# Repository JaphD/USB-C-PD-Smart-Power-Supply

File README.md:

# PD Smart Supply

A USB-C Power Delivery supply designed by Yafet Daniel. Rev A uses an STM32 controller to select a PD voltage, control a protected output, and measure output voltage and current. An OLED and three pushbuttons provide the user interface.

## Specifications

| Parameter | Design specification |
|---|---|
| Input | USB-C Power Delivery through a CH224A controller |
| Output voltage selections | 5 V, 9 V, 12 V, and 20 V |
| Rated output | Up to 3 A total, 60 W at 20 V |
| Output connectors | Two parallel screw terminals sharing one protected output |
| Controller | STM32G071CBT6 |
| Output protection | TPS259470L eFuse with MCU shutdown and fault monitoring |
| Hardware current limit | Approximately 3.76 A nominal; rated output remains 3 A |
| Monitoring | Output voltage and current sensing through the MCU ADC |
| User interface | I²C OLED, Up/Down/Select buttons, and PD status LED |
| Internal power rail | 3.3 V from a TPS560430 buck converter |
| Debug interface | SWD |
| PCB | 70 × 50 mm, four layers, nominal 1.6 mm thickness |

Available output voltages and power depend on the connected PD source and cable. Voltage selection uses discrete PD requests; the design does not provide continuously variable voltage or programmable constant-current regulation. The two outputs share the 3 A rating. The design excludes 15 V and 28 V operation.

## Hardware

The USB-C input feeds the protected output through the eFuse. A separate buck converter powers the controller and interface from the negotiated input voltage. The hardware includes VBUS transient protection, output overvoltage cutoff, controlled startup, and voltage/current test points.

## Project status

The Rev A schematic and four-layer PCB layout are complete and prepared for manufacturing. The repository includes a generated STM32CubeIDE project configured for a 64 MHz system clock, ADC voltage and current sensing, I²C, control and status GPIO, and SWD debugging. PD selection logic, display operation, button handling, and application fault handling remain to be implemented. The ratings above are design targets, not measured performance results.

## Repository contents

- `PD Smart Supply.kicad_pro`, `.kicad_sch`, and `.kicad_pcb`: KiCad project, schematic, and board layout.
- `PD Smart Supply.kicad_dru`: project-specific PCB design rules.
- `Firmware/`: STM32CubeMX configuration, STM32CubeIDE project files, generated firmware sources, and device libraries.
- `Docs/PD_Smart_Supply_Rev_A_Design_Record.pdf`: design record.
- `Docs/Sim/`: LTspice eFuse enable/shutdown simulation.
- `Docs/images/`: PCB layout and 3D render images.

Open `PD Smart Supply.kicad_pro` in KiCad 9 to inspect the hardware. Custom libraries and manufacturer references under `Lib/` and `Docs/Ref/` are excluded from Git, so library paths may need to be restored for editing. Open `Firmware/Firmware.ioc` in STM32CubeMX or import `Firmware/` into STM32CubeIDE to inspect or regenerate the firmware project.

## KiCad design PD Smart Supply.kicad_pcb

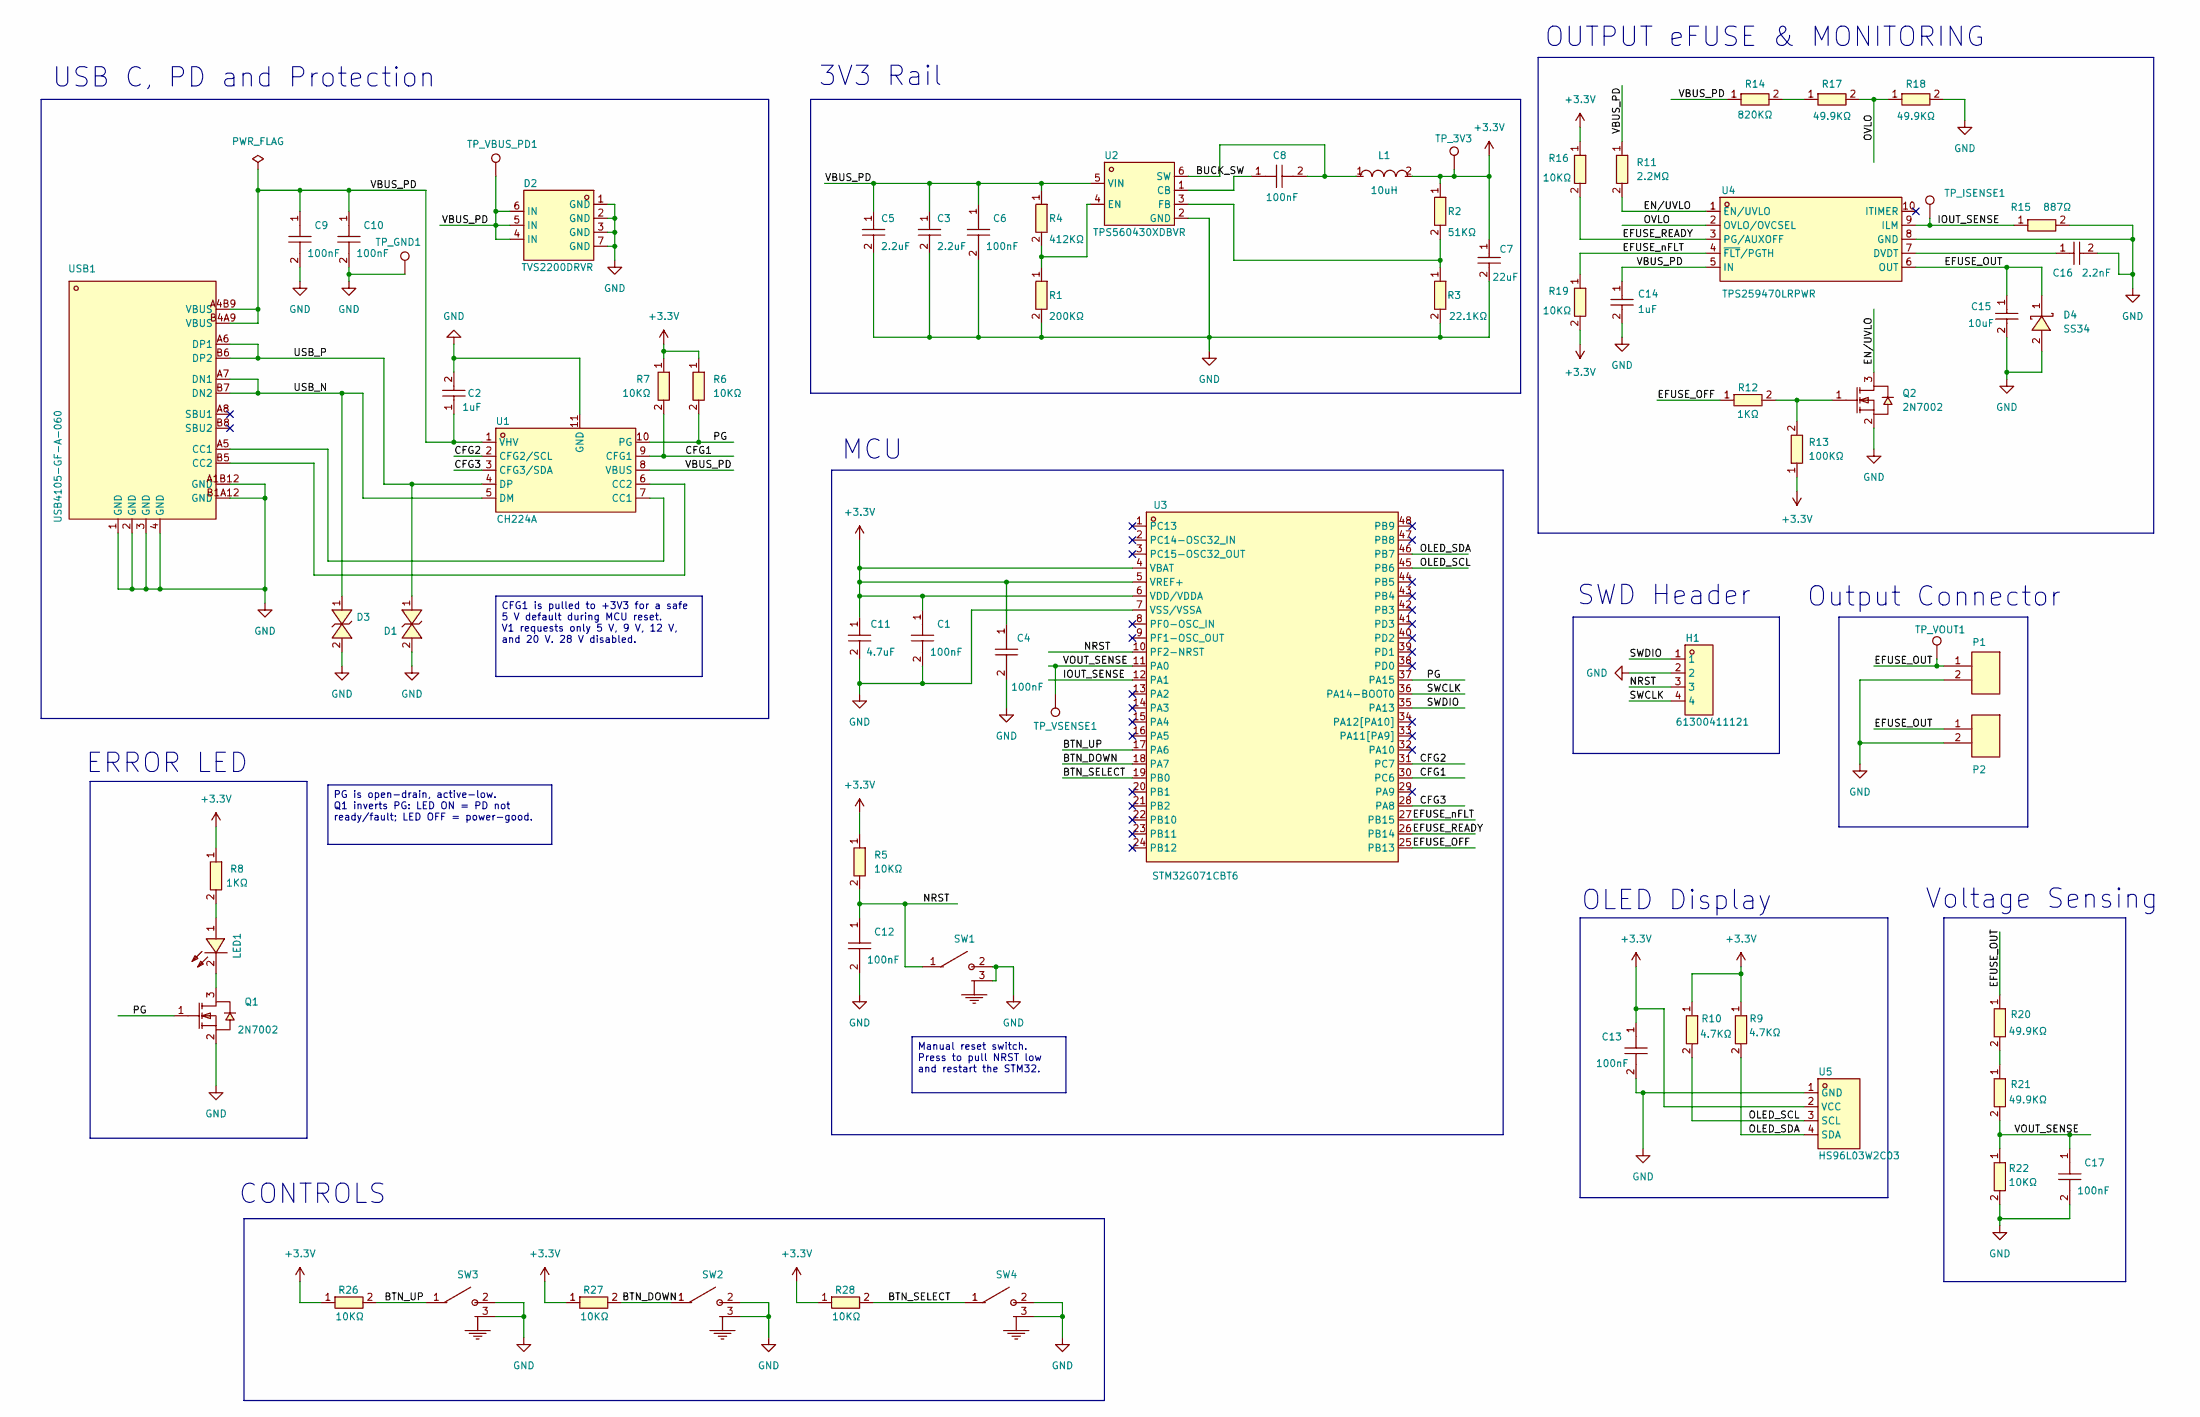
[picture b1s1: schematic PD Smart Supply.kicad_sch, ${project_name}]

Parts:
C1, C4, C6, C8, C9, C10, C12, C13, C17: 100nF; C0603; MPN CC0603KRX7R9BB104; LCSC Part C14663
C2, C14: 1uF; C0805; MPN CL21B105KBFNNNE; LCSC Part C28323
C3, C5: 2.2uF; C1206; MPN CL31B225KBHNNNE; LCSC Part C50254
C7: 22uF; C1206; MPN 1206B226K100NT; LCSC Part C105475
C11: 4.7uF; C0603; MPN CL21A475KAQNNNE; LCSC Part C1779
C15: 10uF; C1210; MPN CL32B106KBJNFNE; LCSC Part C18739
C16: 2.2nF; C0805; MPN CL21C222JBFNNNE; LCSC Part C28260
D1, D3: GG0402052R542P; D0402-BI; MPN GG0402052R542P; LCSC Part C1973257
D2: TVS2200DRVR; WSON-6_L2.0-W2.0-P0.65-BL-EP; MPN TVS2200DRVR; LCSC Part C523793
D4: SS34; SMA_L4.3-W2.6-LS5.2-RD; MPN SS34; LCSC Part C8678
H1: 61300411121; HDR-TH_4P-P2.54-V-M-1; MPN 61300411121; LCSC Part C5184785
L1: 10uH; IND-SMD_L5.0-W5.0_FNR50XXS; MPN FNR5040S100MT; LCSC Part C167967
LED1: KT-0603R; LED-SMD_L1.6-W0.8-R-RD; MPN KT-0603R; LCSC Part C2286
P1, P2: WJ500V-5.08-2P-14-00A; CONN-TH_2P-P5.00_WJ500V-5.08-2P; MPN WJ500V-5.08-2P; LCSC Part C8465
Q1, Q2: 2N7002; SOT-23-3_L2.9-W1.3-P1.90-LS2.4-BR; MPN 2N7002; LCSC Part C8545
R1: 200KΩ; R0603; MPN RS-03K2003FT; LCSC Part C95331
R2: 51KΩ; R0603; MPN 0603WAF5102T5E; LCSC Part C23196
R3: 22.1KΩ; R0603; MPN RC0603FR-0722K1L; LCSC Part C137768
R4: 412KΩ; R0603; MPN 0603WAF4123T5E; LCSC Part C23050
R5, R6, R7, R16, R19, R22, R26, R27, R28: 10KΩ; R0402; MPN 0402WGF1002TCE; LCSC Part C25744
R8, R12: 1KΩ; R0402; MPN 0402WGF1001TCE; LCSC Part C11702
R9, R10: 4.7KΩ; R0402; MPN 0402WGF4701TCE; LCSC Part C25900
R11: 2.2MΩ; R0603; MPN 0603WAF2204T5E; LCSC Part C22938
R13: 100KΩ; R0402; MPN 0402WGF1003TCE; LCSC Part C25741
R14: 820KΩ; R0603; MPN 0603WAF8203T5E; LCSC Part C23252
R15: 887Ω; R0603; MPN 0603WAF8870T5E; LCSC Part C93619
R17, R18, R20, R21: 49.9KΩ; R0603; MPN RC0603FR-0749K9L; LCSC Part C114624
SW1, SW2, SW3, SW4: TSC01-TBW0FH3.5; SW-SMD_XYECONN_TSC01-TBW0FH3.5; MPN TSC01-TBW0FH3.5; LCSC Part C22362977
TP_3V3: TestPoint; TestPoint_Pad_D1.0mm
TP_GND1: TestPoint; TestPoint_Pad_D1.0mm
TP_ISENSE1: TestPoint; TestPoint_Pad_D1.0mm
TP_VBUS_PD1: TestPoint; TestPoint_Pad_D1.0mm
TP_VOUT1: TestPoint; TestPoint_Pad_D1.0mm
TP_VSENSE1: TestPoint; TestPoint_Pad_D1.0mm
U1: CH224A; ESSOP-10_L4.9-W3.9-P1.0-LS6.0-TL-EP; MPN CH224A; LCSC Part C42459160
U2: TPS560430XDBVR; SOT-23-6_L2.9-W1.6-P0.95-LS2.8-BL; MPN TPS560430XDBVR; LCSC Part C524782
U3: STM32G071CBT6; LQFP-48_L7.0-W7.0-P0.50-LS9.0-BL; MPN STM32G071CBT6; LCSC Part C432212
U4: TPS259470LRPWR; VQFN-10_L2.0-W2.0-P0.45-TL; MPN TPS259470LRPWR; LCSC Part C3662793
U5: HS96L03W2C03; OLED-TH_L27.8-W27.2-P2.54_C9900033791; MPN HS96L03W2C03; LCSC Part C5248080
USB1: USB4105-GF-A-060; USB-C-SMD_GT-USB-7010E-1; MPN USB4105-GF-A-060; LCSC Part C3025063

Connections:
+3.3V: C1.1, C4.1, C7.1, C11.1, C13.1, L1.2, R2.1, R5.1, R6.1, R7.1, R8.1, R9.1, R10.1, R13.1, R16.1, R19.2, R26.1, R27.1, R28.1, TP_3V3.1, U3.4 (VBAT), U3.5 (VREF+), U3.6 (VDD/VDDA), U5.2 (VCC)
/BTN_DOWN: R27.2, SW2.1, U3.18 (PA7)
/BTN_SELECT: R28.2, SW4.1, U3.19 (PB0)
/BTN_UP: R26.2, SW3.1, U3.17 (PA6)
/BUCK_SW: C8.2, L1.1, U2.6 (SW)
/CFG1: R7.2, U1.9 (CFG1), U3.30 (PC6)
/CFG2: U1.2 (CFG2/SCL), U3.31 (PC7)
/CFG3: U1.3 (CFG3/SDA), U3.28 (PA8)
/EFUSE_OFF: R12.1, U3.25 (PB13)
/EFUSE_OUT: C15.1, D4.1, P1.1, P2.1, R20.1, TP_VOUT1.1, U4.6 (OUT)
/EFUSE_READY: R16.2, U3.26 (PB14), U4.3 (PG/AUXOFF)
/EFUSE_nFLT: R19.1, U3.27 (PB15), U4.4 (~FLT/PGTH)
/EN/UVLO: Q2.3, R11.2, U4.1 (EN/UVLO)
/IOUT_SENSE: R15.1, TP_ISENSE1.1, U3.12 (PA1), U4.9 (ILM)
/NRST: C12.1, H1.3, R5.2, SW1.1, U3.10 (PF2-NRST)
/OLED_SCL: R10.2, U3.45 (PB6), U5.3 (SCL)
/OLED_SDA: R9.2, U3.46 (PB7), U5.4 (SDA)
/OVLO: R17.2, R18.1, U4.2 (OVLO/OVCSEL)
/PG: Q1.1, R6.2, U1.10 (PG), U3.37 (PA15)
/SWCLK: H1.4, U3.36 (PA14-BOOT0)
/SWDIO: H1.1, U3.35 (PA13)
/USB_N: D3.1, U1.5 (DM), USB1.A7 (DN1), USB1.B7 (DN2)
/USB_P: D1.1, U1.4 (DP), USB1.A6 (DP1), USB1.B6 (DP2)
/VBUS_PD: C2.1, C3.1, C5.1, C6.1, C9.1, C10.1, C14.1, D2.4 (IN), D2.5 (IN), D2.6 (IN), R4.1, R11.1, R14.1, TP_VBUS_PD1.1, U1.1 (VHV), U1.8 (VBUS), U2.5 (VIN), U4.5 (IN), USB1.A4B9 (VBUS), USB1.B4A9 (VBUS)
/VOUT_SENSE: C17.1, R21.2, R22.1, TP_VSENSE1.1, U3.11 (PA0)
GND: C1.2, C2.2, C3.2, C4.2, C5.2, C6.2, C7.2, C9.2, C10.2, C11.2, C12.2, C13.2, C14.2, C15.2, C16.2, C17.2, D1.2, D2.1 (GND), D2.2 (GND), D2.3 (GND), D2.7 (GND), D3.2, D4.2, H1.2, P1.2, P2.2, Q1.2, Q2.2, R1.2, R3.2, R15.2, R18.2, R22.2, SW1.2, SW1.3, SW2.2, SW2.3, SW3.2, SW3.3, SW4.2, SW4.3, TP_GND1.1, U1.11 (GND), U2.2 (GND), U3.7 (VSS/VSSA), U4.8 (GND), U5.1 (GND), USB1.1 (GND), USB1.2 (GND), USB1.3 (GND), USB1.4 (GND), USB1.A1B12 (GND), USB1.B1A12 (GND)
unnamed: LED1.1, R8.2
unnamed: LED1.2, Q1.3
unnamed: Q2.1, R12.2, R13.2
unnamed: R14.2, R17.1
unnamed: R20.2, R21.1
unnamed: U1.7 (CC1), USB1.A5 (CC1)
unnamed: U1.6 (CC2), USB1.B5 (CC2)
unnamed: C8.1, U2.1 (CB)
unnamed: R1.1, R4.2, U2.4 (EN)
unnamed: R2.2, R3.1, U2.3 (FB)
unnamed: C16.1, U4.7 (DVDT)

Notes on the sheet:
MCU
USB C, PD and Protection
OLED Display
Output Connector
ERROR LED
OUTPUT eFUSE & MONITORING
CONTROLS
SWD Header
Voltage Sensing
3V3 Rail
CFG1 is pulled to +3V3 for a safe 5 V default during MCU reset. V1 requests only 5 V, 9 V, 12 V, and 20 V. 28 V disabled.
Manual reset switch. Press to pull NRST low and restart the STM32.
PG is open-drain, active-low. Q1 inverts PG: LED ON = PD not ready/fault; LED OFF = power-good.

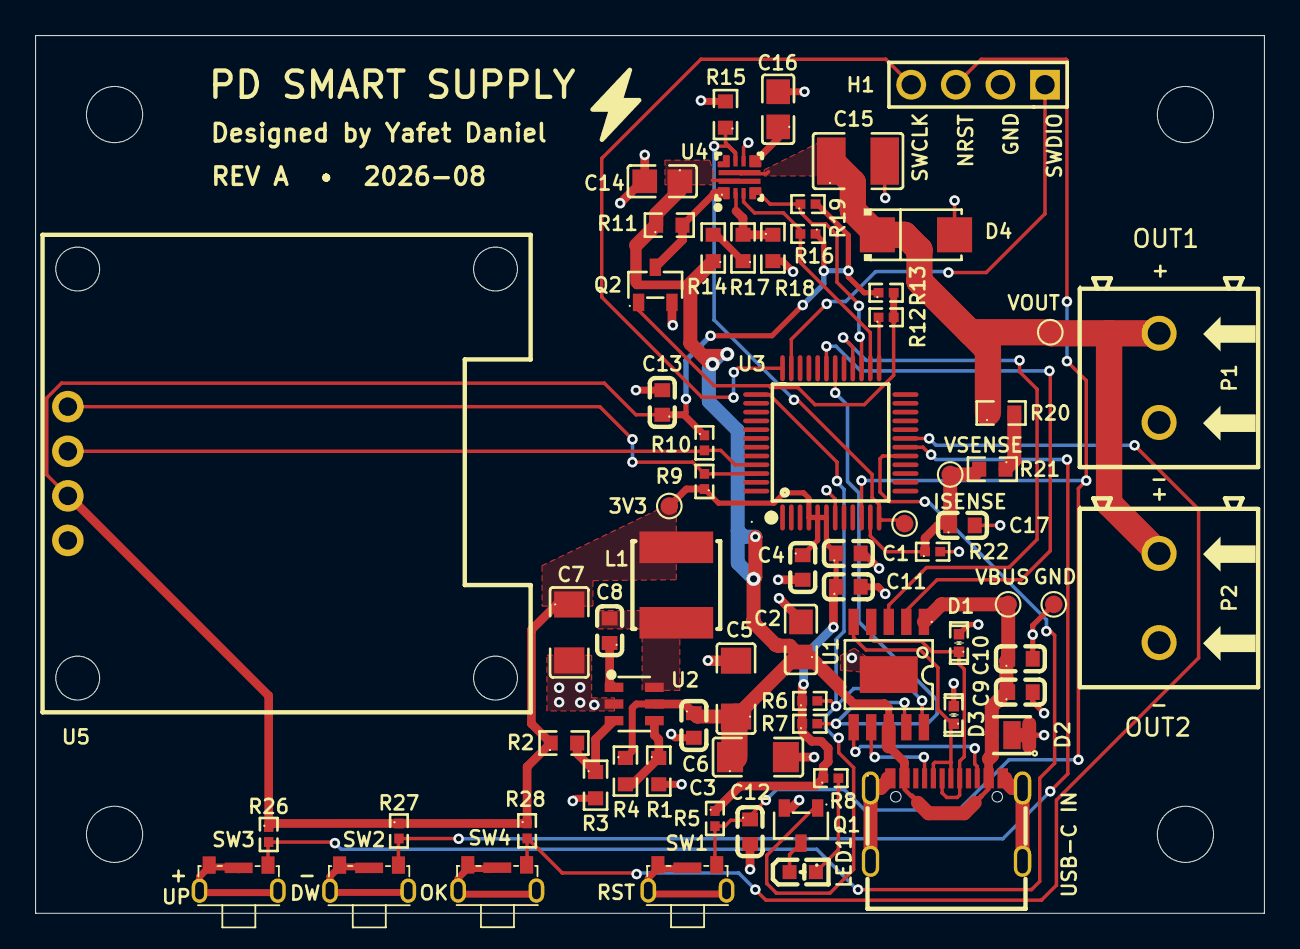
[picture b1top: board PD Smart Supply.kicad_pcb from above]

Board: 4 copper layers, 70.0 x 50.0 mm, 69 parts (0 on the bottom side), 37 nets.

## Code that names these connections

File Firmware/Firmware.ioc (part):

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Mcu.Name=STM32G071C(6-8-B)Tx
Mcu.Package=LQFP48
Mcu.UserName=STM32G071CBTx
PA0.Mode=IN0
PA0.Signal=ADC1_IN0
PA1.Mode=IN1
PA1.Signal=ADC1_IN1
PA13.Mode=Serial_Wire
PA13.Signal=SYS_SWDIO
PA14-BOOT0.Mode=Serial_Wire
PA14-BOOT0.Signal=SYS_SWCLK
PA15.GPIOParameters=GPIO_Label
PA15.GPIO_Label=PD_PG
PA15.Signal=GPIO_Input
PA6.GPIOParameters=GPIO_Label
PA6.GPIO_Label=BTN_UP
PA6.Signal=GPIO_Input
PA7.GPIOParameters=GPIO_Label
PA7.GPIO_Label=BTN_DOWN
PA7.Signal=GPIO_Input
PA8.GPIOParameters=PinState,GPIO_Label
PA8.GPIO_Label=CFG3
PA8.PinState=GPIO_PIN_SET
PA8.Signal=GPIO_Output
PB0.GPIOParameters=GPIO_Label
PB0.GPIO_Label=BTN_SELECT
PB0.Signal=GPIO_Input
PB13.GPIOParameters=PinState,GPIO_Label
PB13.GPIO_Label=EFUSE_OFF
PB13.PinState=GPIO_PIN_SET
PB13.Signal=GPIO_Output
PB14.GPIOParameters=GPIO_Label
PB14.GPIO_Label=EFUSE_READY
PB14.Signal=GPIO_Input
PB15.GPIOParameters=GPIO_Label
PB15.GPIO_Label=EFUSE_nFLT
PB15.Signal=GPIO_Input
PB6.Mode=I2C
PB6.Signal=I2C1_SCL
PB7.Mode=I2C
PB7.Signal=I2C1_SDA
PC6.GPIOParameters=PinState,GPIO_Label
PC6.GPIO_Label=CFG1
PC6.PinState=GPIO_PIN_SET
PC6.Signal=GPIO_Output
PC7.GPIOParameters=PinState,GPIO_Label
PC7.GPIO_Label=CFG2
PC7.PinState=GPIO_PIN_SET
PC7.Signal=GPIO_Output
RCC.HSE_VALUE=8000000
RCC.SYSCLKFreq_VALUE=64000000
RCC.SYSCLKSource=RCC_SYSCLKSOURCE_PLLCLK
board=custom
